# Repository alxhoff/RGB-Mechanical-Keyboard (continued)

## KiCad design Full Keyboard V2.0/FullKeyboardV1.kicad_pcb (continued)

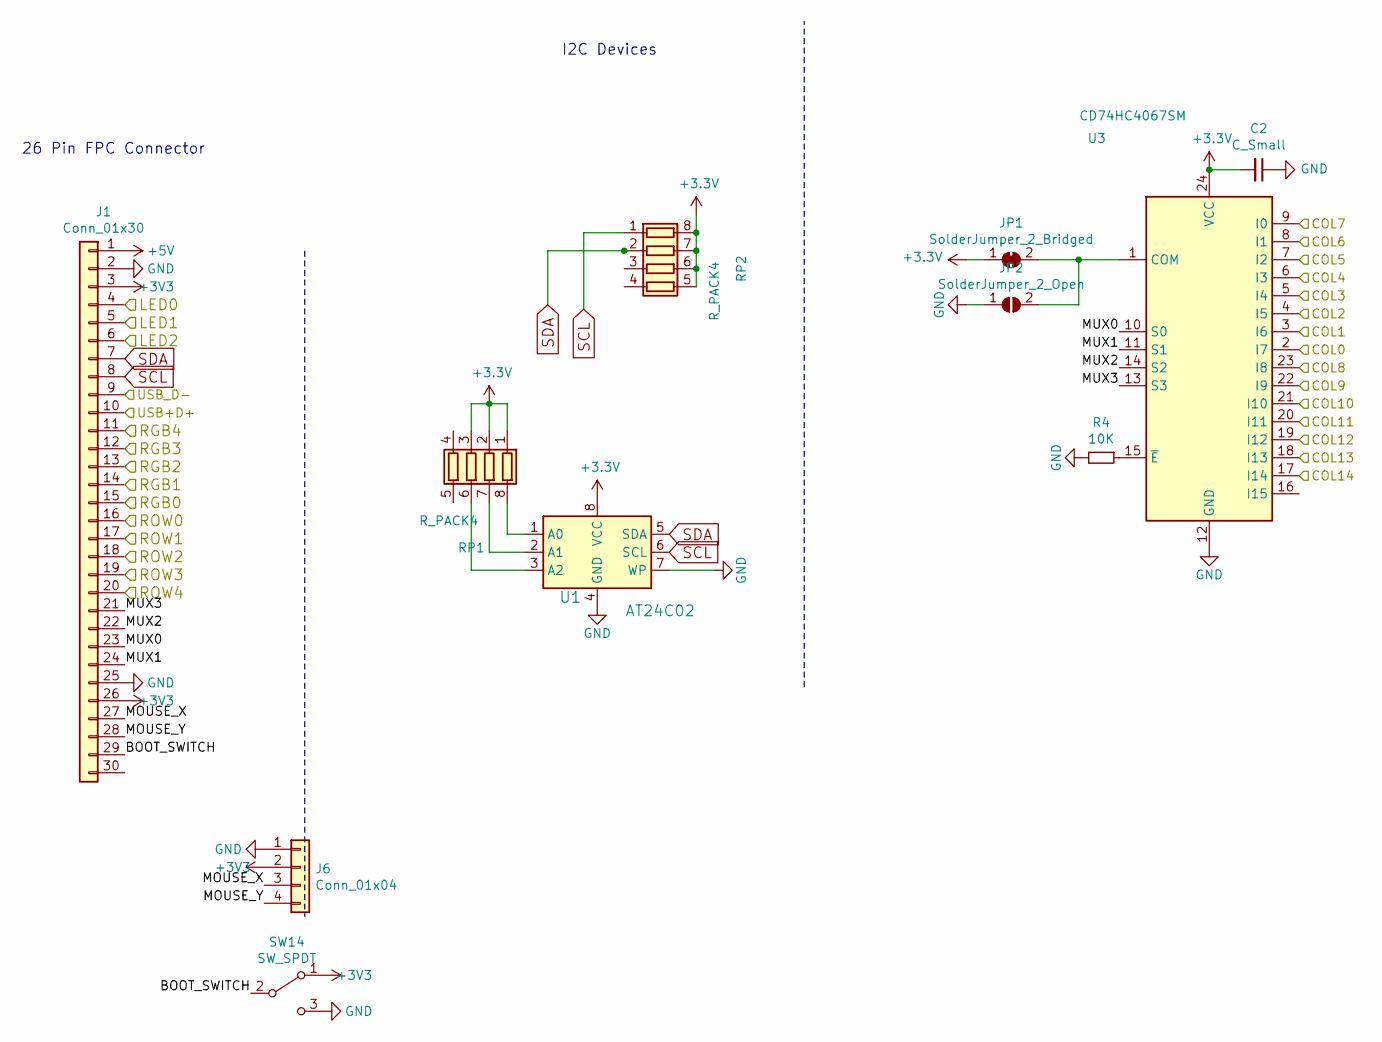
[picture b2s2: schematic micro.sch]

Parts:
C2: C_Small; C_0603_1608Metric
J1: Conn_01x30; Hirose_FH12-30S-0.5SH_1x30-1MP_P0.50mm_Horizontal
J6: Conn_01x04; JST_PH_S4B-PH-SM4-TB_1x04-1MP_P2.00mm_Horizontal
JP1: SolderJumper_2_Bridged; SolderJumper-2_P1.3mm_Bridged_RoundedPad1.0x1.5mm
JP2: SolderJumper_2_Open; SolderJumper-2_P1.3mm_Open_RoundedPad1.0x1.5mm
R4: 10K; R_0603_1608Metric
RP1, RP2: R_PACK4; R_Array_Concave_4x0402
SW14: SW_SPDT; SS12F23
U1: AT24C02; SOP-8_3.9x4.9mm_P1.27mm
U3: CD74HC4067SM; SSOP-24_5.3x8.2mm_P0.65mm

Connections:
+5V: J1.1; also elsewhere on the board
/COL0: U3.2 (I7); also elsewhere on the board
/COL1: U3.3 (I6); also elsewhere on the board
/COL2: U3.4 (I5); also elsewhere on the board
/COL3: U3.5 (I4); also elsewhere on the board
/COL4: U3.6 (I3); also elsewhere on the board
/COL5: U3.7 (I2); also elsewhere on the board
/COL6: U3.8 (I1); also elsewhere on the board
/COL7: U3.9 (I0); also elsewhere on the board
/COL8: U3.23 (I8); also elsewhere on the board
/COL9: U3.22 (I9); also elsewhere on the board
/COL10: U3.21 (I10); also elsewhere on the board
/COL11: U3.20 (I11); also elsewhere on the board
/COL12: U3.19 (I12); also elsewhere on the board
/COL13: U3.18 (I13); also elsewhere on the board
/COL14: U3.17 (I14); also elsewhere on the board
/LED0: J1.4; also elsewhere on the board
/LED1: J1.5; also elsewhere on the board
/LED2: J1.6; also elsewhere on the board
/MicroSheet/BOOT_SWITCH: J1.29, SW14.2 (B)
/MicroSheet/MOUSE_X: J1.27, J6.3
/MicroSheet/MOUSE_Y: J1.28, J6.4
/MicroSheet/MUX0: J1.23, U3.10 (S0)
/MicroSheet/MUX1: J1.24, U3.11 (S1)
/MicroSheet/MUX2: J1.22, U3.14 (S2)
/MicroSheet/MUX3: J1.21, U3.13 (S3)
/MicroSheet/USB+D+: J1.10; also elsewhere on the board
/MicroSheet/USB_D-: J1.9; also elsewhere on the board
/RGB0: J1.15; also elsewhere on the board
/RGB1: J1.14; also elsewhere on the board
/RGB2: J1.13; also elsewhere on the board
/RGB3: J1.12; also elsewhere on the board
/RGB4: J1.11; also elsewhere on the board
/ROW0: J1.16; also elsewhere on the board
/ROW1: J1.17; also elsewhere on the board
/ROW2: J1.18; also elsewhere on the board
/ROW3: J1.19; also elsewhere on the board
/ROW4: J1.20; also elsewhere on the board
GND: C2.1, J1.2, J1.25, J6.1, JP2.1 (A), R4.2, SW14.3 (C), U1.4 (GND), U1.7 (WP), U3.12 (GND); also elsewhere on the board
unnamed: JP1.2 (B), JP2.2 (B), U3.1 (COM)
unnamed: R4.1, U3.15 (~E)
unnamed: RP1.6 (R3.2), U1.3 (A2)
unnamed: RP1.7 (R2.2), U1.2 (A1)
unnamed: RP1.8 (R1.2), U1.1 (A0)
SCL: J1.8, RP2.1 (R1.1), U1.6 (SCL)
SDA: J1.7, RP2.2 (R2.1), U1.5 (SDA)

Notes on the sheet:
I2C Devices
26 Pin FPC Connector

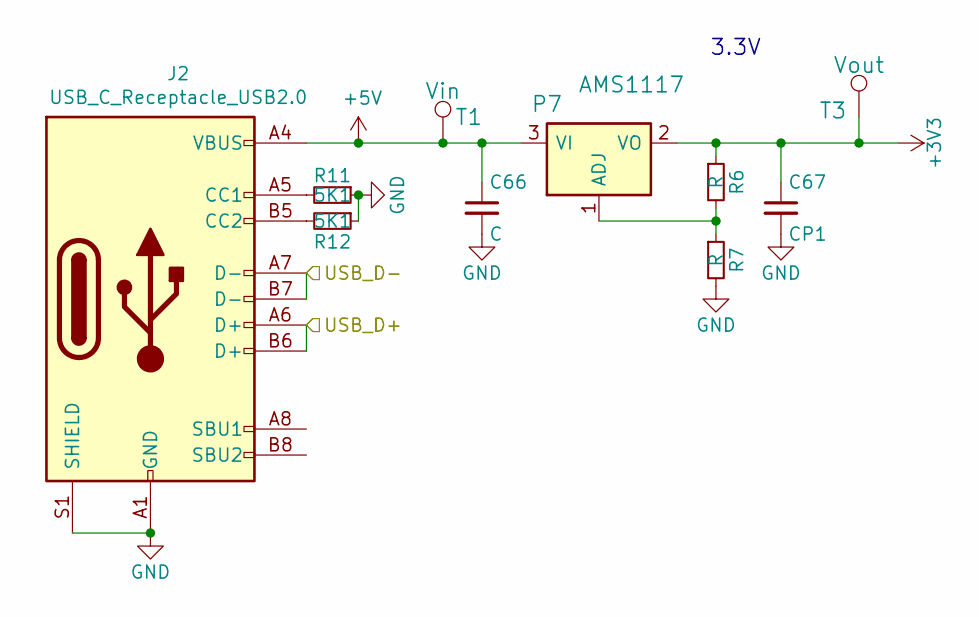
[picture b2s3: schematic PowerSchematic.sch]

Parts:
C66: C; C_0603_1608Metric
C67: CP1; C_0603_1608Metric
J2: USB_C_Receptacle_USB2.0; USB_C_Receptacle_HRO_TYPE-C-31-M-12
P7: AMS1117; SOT-223
R6, R7: R; R_0603_1608Metric
R11, R12: 5K1; R_0603_1608Metric
T1: Vin; TestPoint_Pad_1.0x1.0mm
T3: Vout; TestPoint_Pad_1.0x1.0mm

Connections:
+5V: C66.1, J2.A4 (VBUS), J2.A9 (VBUS), J2.B4 (VBUS), J2.B9 (VBUS), P7.3 (VI), T1.1; also elsewhere on the board
/PowerSheet/USB_D+: J2.A6 (D+), J2.B6 (D+); also elsewhere on the board
/PowerSheet/USB_D-: J2.A7 (D-), J2.B7 (D-); also elsewhere on the board
GND: C66.2, C67.2, J2.A1 (GND), J2.A12 (GND), J2.B1 (GND), J2.B12 (GND), J2.S1 (SHIELD), R7.2, R11.1, R12.1; also elsewhere on the board
unnamed: J2.A5 (CC1), R11.2
unnamed: J2.B5 (CC2), R12.2
unnamed: P7.1 (ADJ), R6.2, R7.1

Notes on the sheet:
3.3V

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
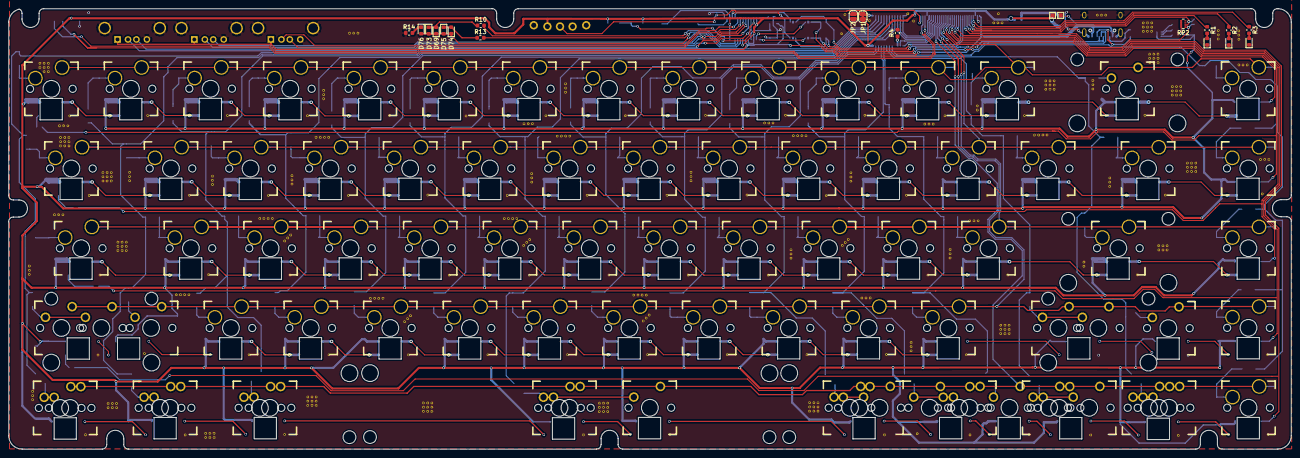
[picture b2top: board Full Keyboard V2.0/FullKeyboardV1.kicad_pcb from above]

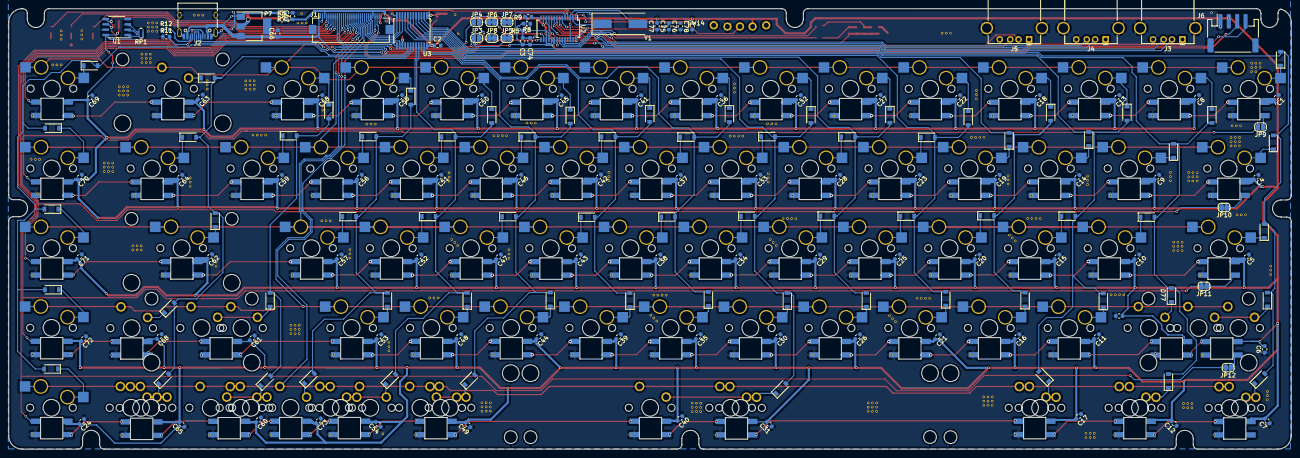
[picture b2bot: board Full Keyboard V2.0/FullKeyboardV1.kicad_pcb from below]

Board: 2 copper layers, 305.6 x 104.9 mm, 257 parts (178 on the bottom side), 214 nets.

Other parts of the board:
C3, C76, C77: 0.1uF; C_0603_1608Metric
C74, C75, C78: 10uF; C_0603_1608Metric
D69, D73, D74, D75: Green; LED_0603_1608Metric
D76: Red; LED_0603_1608Metric
J3, J4, J5: USB_A; USB_A_Stewart_SS-52100-001_Horizontal
JP9, JP10, JP11, JP12: SolderJumper_2_Open; SolderJumper-2_P1.3mm_Open_RoundedPad1.0x1.5mm
R5: 100K; R_0603_1608Metric
R8: 47K; R_0603_1608Metric
R9: 2K7; R_0603_1608Metric
R10, R13, R14: 330; R_0603_1608Metric
U2: FE1.1s; SSOP-28_3.9x9.9mm_P0.635mm
Y1: 12MHz; Crystal_SMD_HC49-SD

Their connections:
+5V: C3.2, C74.2, J3.1, J4.1, J5.1, R8.2, U2.20; also elsewhere on the board
/RGB0_OUT: JP9.1; also elsewhere on the board
/RGB1: JP9.2; also elsewhere on the board
/RGB1_OUT: JP10.1; also elsewhere on the board
/RGB2: JP10.2; also elsewhere on the board
/RGB2_OUT: JP11.1; also elsewhere on the board
/RGB3: JP11.2; also elsewhere on the board
/RGB3_OUT: JP12.1; also elsewhere on the board
/RGB4: JP12.2; also elsewhere on the board
/usb_hub/Din+: U2.5; also elsewhere on the board
/usb_hub/Din-: U2.4; also elsewhere on the board
/usb_hub/Dout+: U2.16; also elsewhere on the board
/usb_hub/Dout-: U2.15; also elsewhere on the board
GND: C3.1, C74.1, C75.1, C76.1, C77.1, C78.1, J3.4, J3.5, J4.4, J4.5, J5.4, J5.5, R5.2, R9.2, R14.1, U2.1; also elsewhere on the board
unnamed: C75.2, C76.2, U2.12, U2.28
unnamed: D69.1, D73.2, D74.1, D75.2, D76.2, U2.22
unnamed: D69.2, D73.1, R10.1
unnamed: D74.2, D75.1, R13.1
unnamed: D76.1, R14.2
unnamed: J3.2, U2.10
unnamed: J3.3, U2.11
unnamed: J4.2, U2.8
unnamed: J4.3, U2.9
unnamed: J5.2, U2.6
unnamed: J5.3, U2.7
unnamed: R5.1, R8.1, U2.18
unnamed: R9.1, U2.14
unnamed: R10.2, U2.24
unnamed: R13.2, U2.23
unnamed: U2.2, Y1.1
unnamed: U2.3, Y1.2

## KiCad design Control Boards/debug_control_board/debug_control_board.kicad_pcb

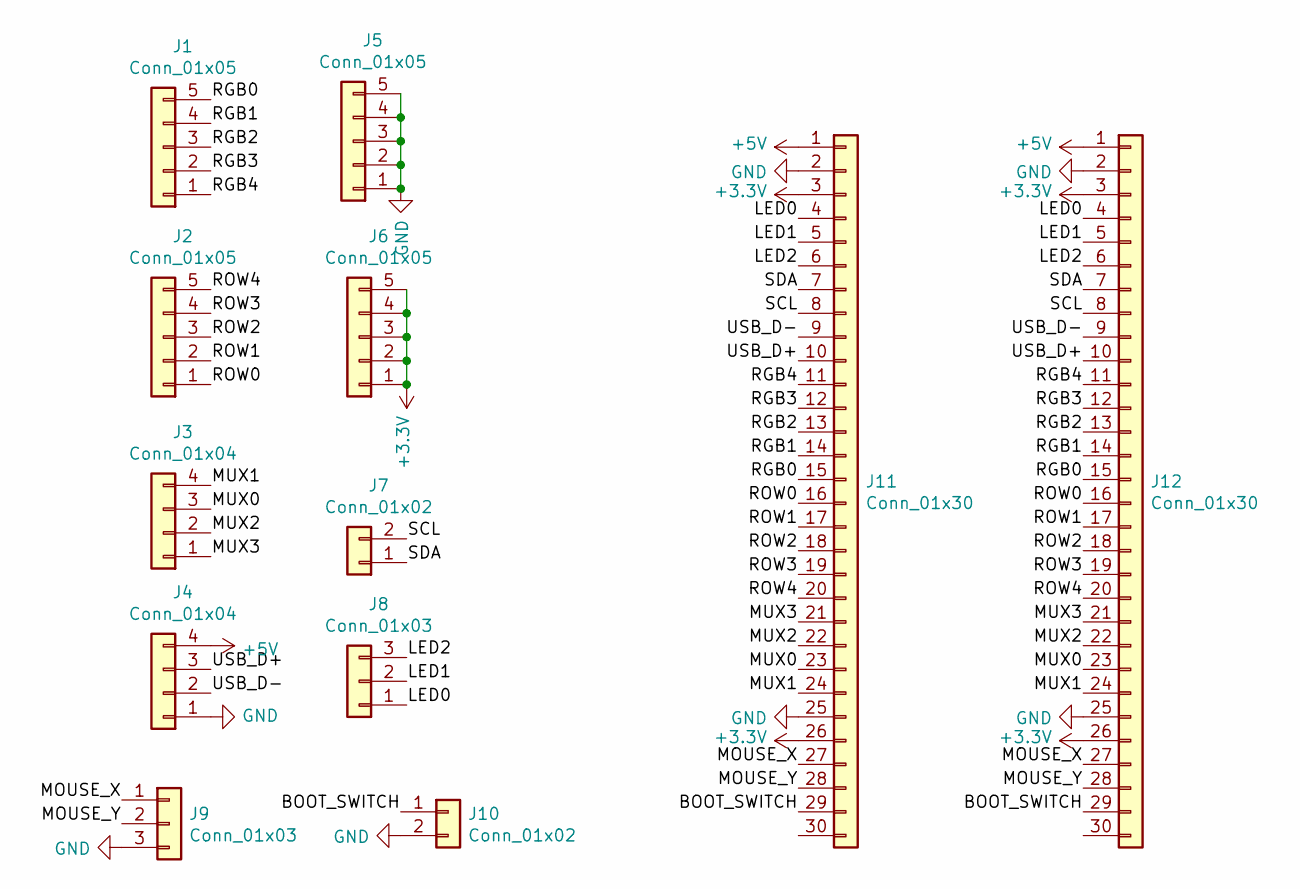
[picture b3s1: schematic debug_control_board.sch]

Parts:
J1, J2, J5, J6: Conn_01x05; PinHeader_1x05_P2.54mm_Vertical
J3, J4: Conn_01x04; PinHeader_1x04_P2.54mm_Vertical
J7, J10: Conn_01x02; PinHeader_1x02_P2.54mm_Vertical
J8, J9: Conn_01x03; PinHeader_1x03_P2.54mm_Vertical
J11, J12: Conn_01x30; Hirose_FH12-30S-0.5SH_1x30-1MP_P0.50mm_Horizontal

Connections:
+3V3: J6.1, J6.2, J6.3, J6.4, J6.5, J11.3, J11.26, J12.3, J12.26
+5V: J4.4, J11.1, J12.1
/BOOT_SWITCH: J10.1, J11.29, J12.29
/LED0: J8.1, J11.4, J12.4
/LED1: J8.2, J11.5, J12.5
/LED2: J8.3, J11.6, J12.6
/MOUSE_X: J9.1, J11.27, J12.27
/MOUSE_Y: J9.2, J11.28, J12.28
/MUX0: J3.3, J11.23, J12.23
/MUX1: J3.4, J11.24, J12.24
/MUX2: J3.2, J11.22, J12.22
/MUX3: J3.1, J11.21, J12.21
/RGB0: J1.5, J11.15, J12.15
/RGB1: J1.4, J11.14, J12.14
/RGB2: J1.3, J11.13, J12.13
/RGB3: J1.2, J11.12, J12.12
/RGB4: J1.1, J11.11, J12.11
/ROW0: J2.1, J11.16, J12.16
/ROW1: J2.2, J11.17, J12.17
/ROW2: J2.3, J11.18, J12.18
/ROW3: J2.4, J11.19, J12.19
/ROW4: J2.5, J11.20, J12.20
/SCL: J7.2, J11.8, J12.8
/SDA: J7.1, J11.7, J12.7
/USB_D+: J4.3, J11.10, J12.10
/USB_D-: J4.2, J11.9, J12.9
GND: J4.1, J5.1, J5.2, J5.3, J5.4, J5.5, J9.3, J10.2, J11.2, J11.25, J12.2, J12.25

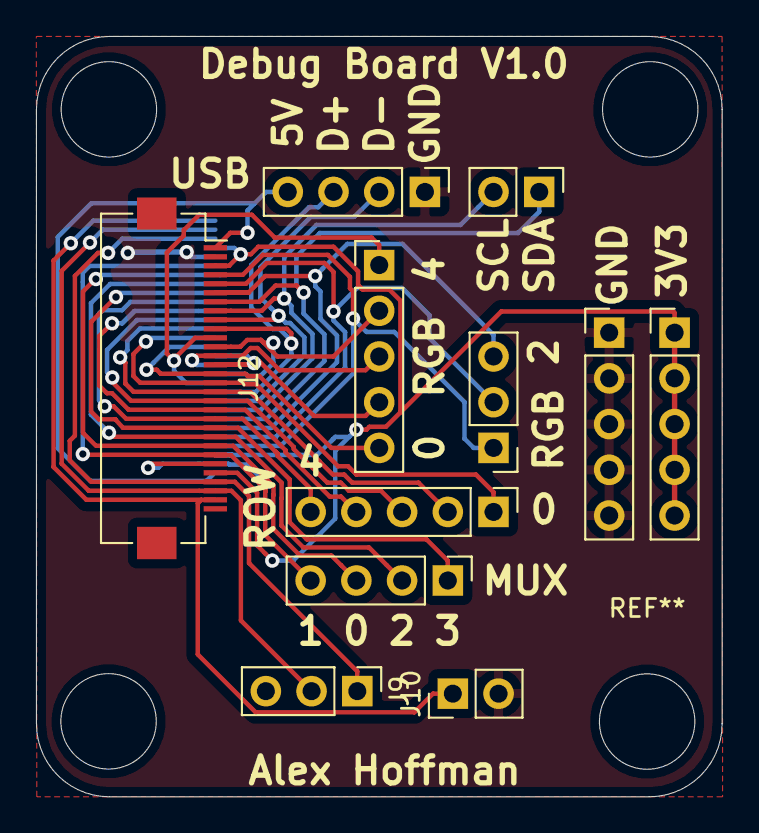
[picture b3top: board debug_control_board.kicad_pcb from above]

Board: 2 copper layers, 38.1 x 42.2 mm, 12 parts (1 on the bottom side), 27 nets.

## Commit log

2020-04-10 Added idea to README
2020-04-13 Added USB HUB
2020-04-14 Added multi-function left and right shift
2020-04-22 Added solder jumpers to allow for daisy chaining RGB rows
2020-04-22 Updated footprints on keyboard PCB
2020-04-22 Updated bluepill board for 30pin ribbon cable
2020-04-22 Added BOOT switch
2020-04-22 Updated debug board to support 30 pin ribbon cable
2020-04-24 added hotswap sockets
2020-04-25 Modified mounting holes
2022-06-13 Started test pad
2022-06-16 Started nucleo 144 test pad and keypad boards
